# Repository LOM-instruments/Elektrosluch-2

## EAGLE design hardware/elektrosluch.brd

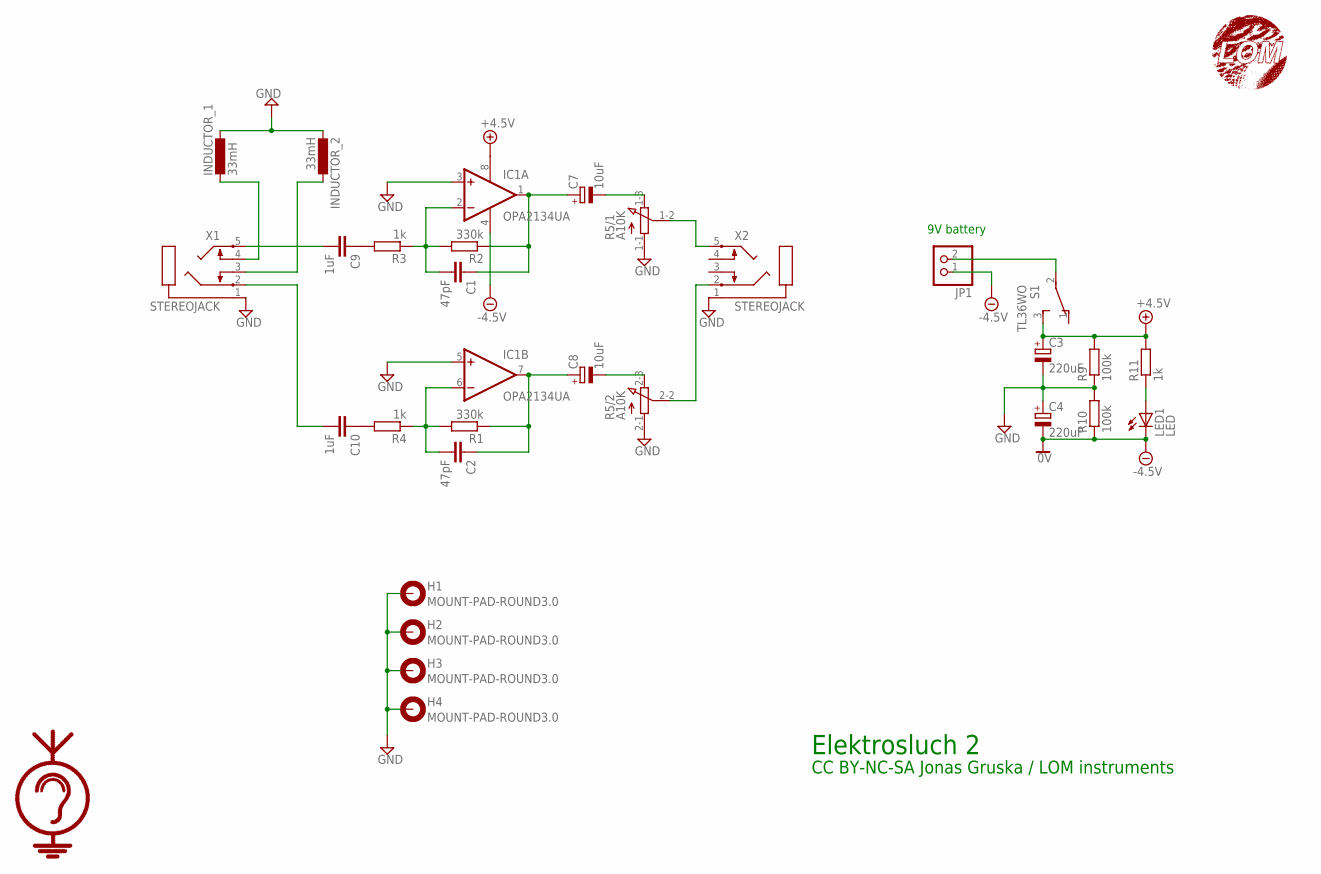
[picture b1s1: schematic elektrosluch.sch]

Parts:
C1, C2: 47pF; C1206
C3, C4: 220uF; PANASONIC_D
C7, C8: 10uF; PANASONIC_B
C9, C10: 1uF; C1812
H1, H2, H3, H4: MOUNT-PAD-ROUND3.0; 3,0-PAD
IC1: OPA2134UA; SO08
INDUCTOR_1, INDUCTOR_2: 33mH; COIL
JP1: PINHD-1X2; 1X02
LED1: LED; LED3MM
R1, R2: 330k; M1206
R3, R4, R11: 1k; M1206
R5: A10K; 3RP/1610G
R9, R10: 100k; M1206
S1: TL36WO; TL3XWO
U$3: LOM; LOMLOGO
U$5: ELEKTROSLUCH
X1, X2: STEREOJACK; STX3100

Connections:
+5V: C3.+, IC1.8 (V+), R9.2, R11.2, S1.3 (S)
-5V: C4.-, IC1.4 (V-), JP1.1, LED1.K (C), R10.1
GND: C3.-, C4.+, H1.B3,0, H2.B3,0, H3.B3,0, H4.B3,0, IC1.3 (+IN), IC1.5 (+IN), INDUCTOR_1.P$1 (1), INDUCTOR_2.P$2 (2), R5.1-1 (1), R5.2-1 (1), R9.1, R10.2, X1.1, X2.1
unnamed: C1.2, IC1.2 (-IN), R2.2, R3.1
unnamed: C1.1, C7.+, IC1.1 (OUT), R2.1
unnamed: C7.-, R5.1-3 (3)
unnamed: C2.2, IC1.6 (-IN), R1.2, R4.1
unnamed: C2.1, C8.+, IC1.7 (OUT), R1.1
unnamed: C8.-, R5.2-3 (3)
unnamed: R5.1-2 (2), X2.5
unnamed: C9.2, X1.5
unnamed: R5.2-2 (2), X2.2
unnamed: C10.2, X1.2
unnamed: C9.1, R3.2
unnamed: INDUCTOR_1.P$2 (2), X1.4
unnamed: INDUCTOR_2.P$1 (1), X1.3
unnamed: LED1.A, R11.1
unnamed: C10.1, R4.2
unnamed: JP1.2, S1.2

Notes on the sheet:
9V battery
Elektrosluch 2
CC BY-NC-SA Jonas Gruska / LOM instruments

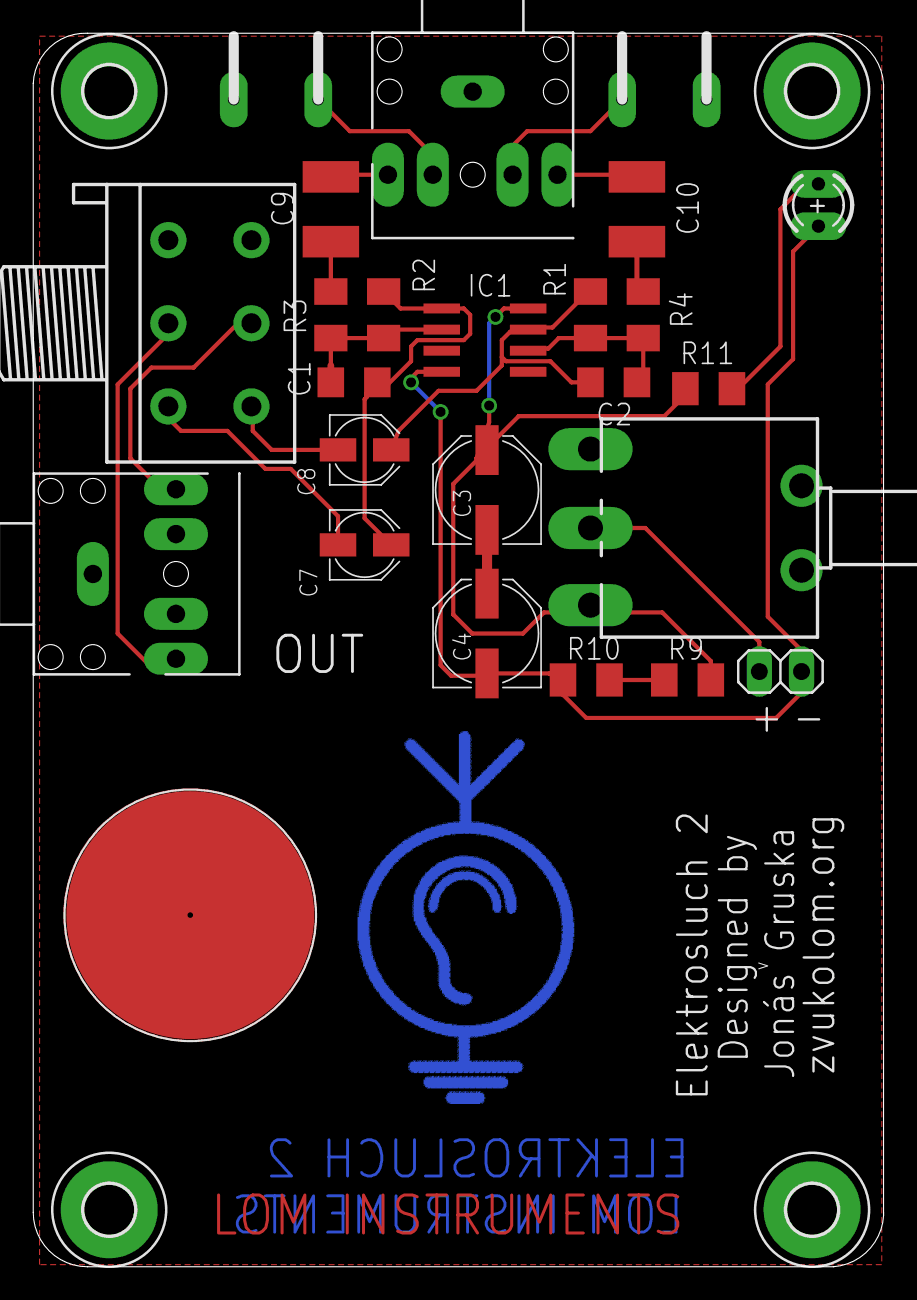
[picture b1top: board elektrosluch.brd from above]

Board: 2 copper layers, 51.2 x 74.2 mm, 30 parts (0 on the bottom side), 19 nets.

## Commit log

2014-04-13 we're up
